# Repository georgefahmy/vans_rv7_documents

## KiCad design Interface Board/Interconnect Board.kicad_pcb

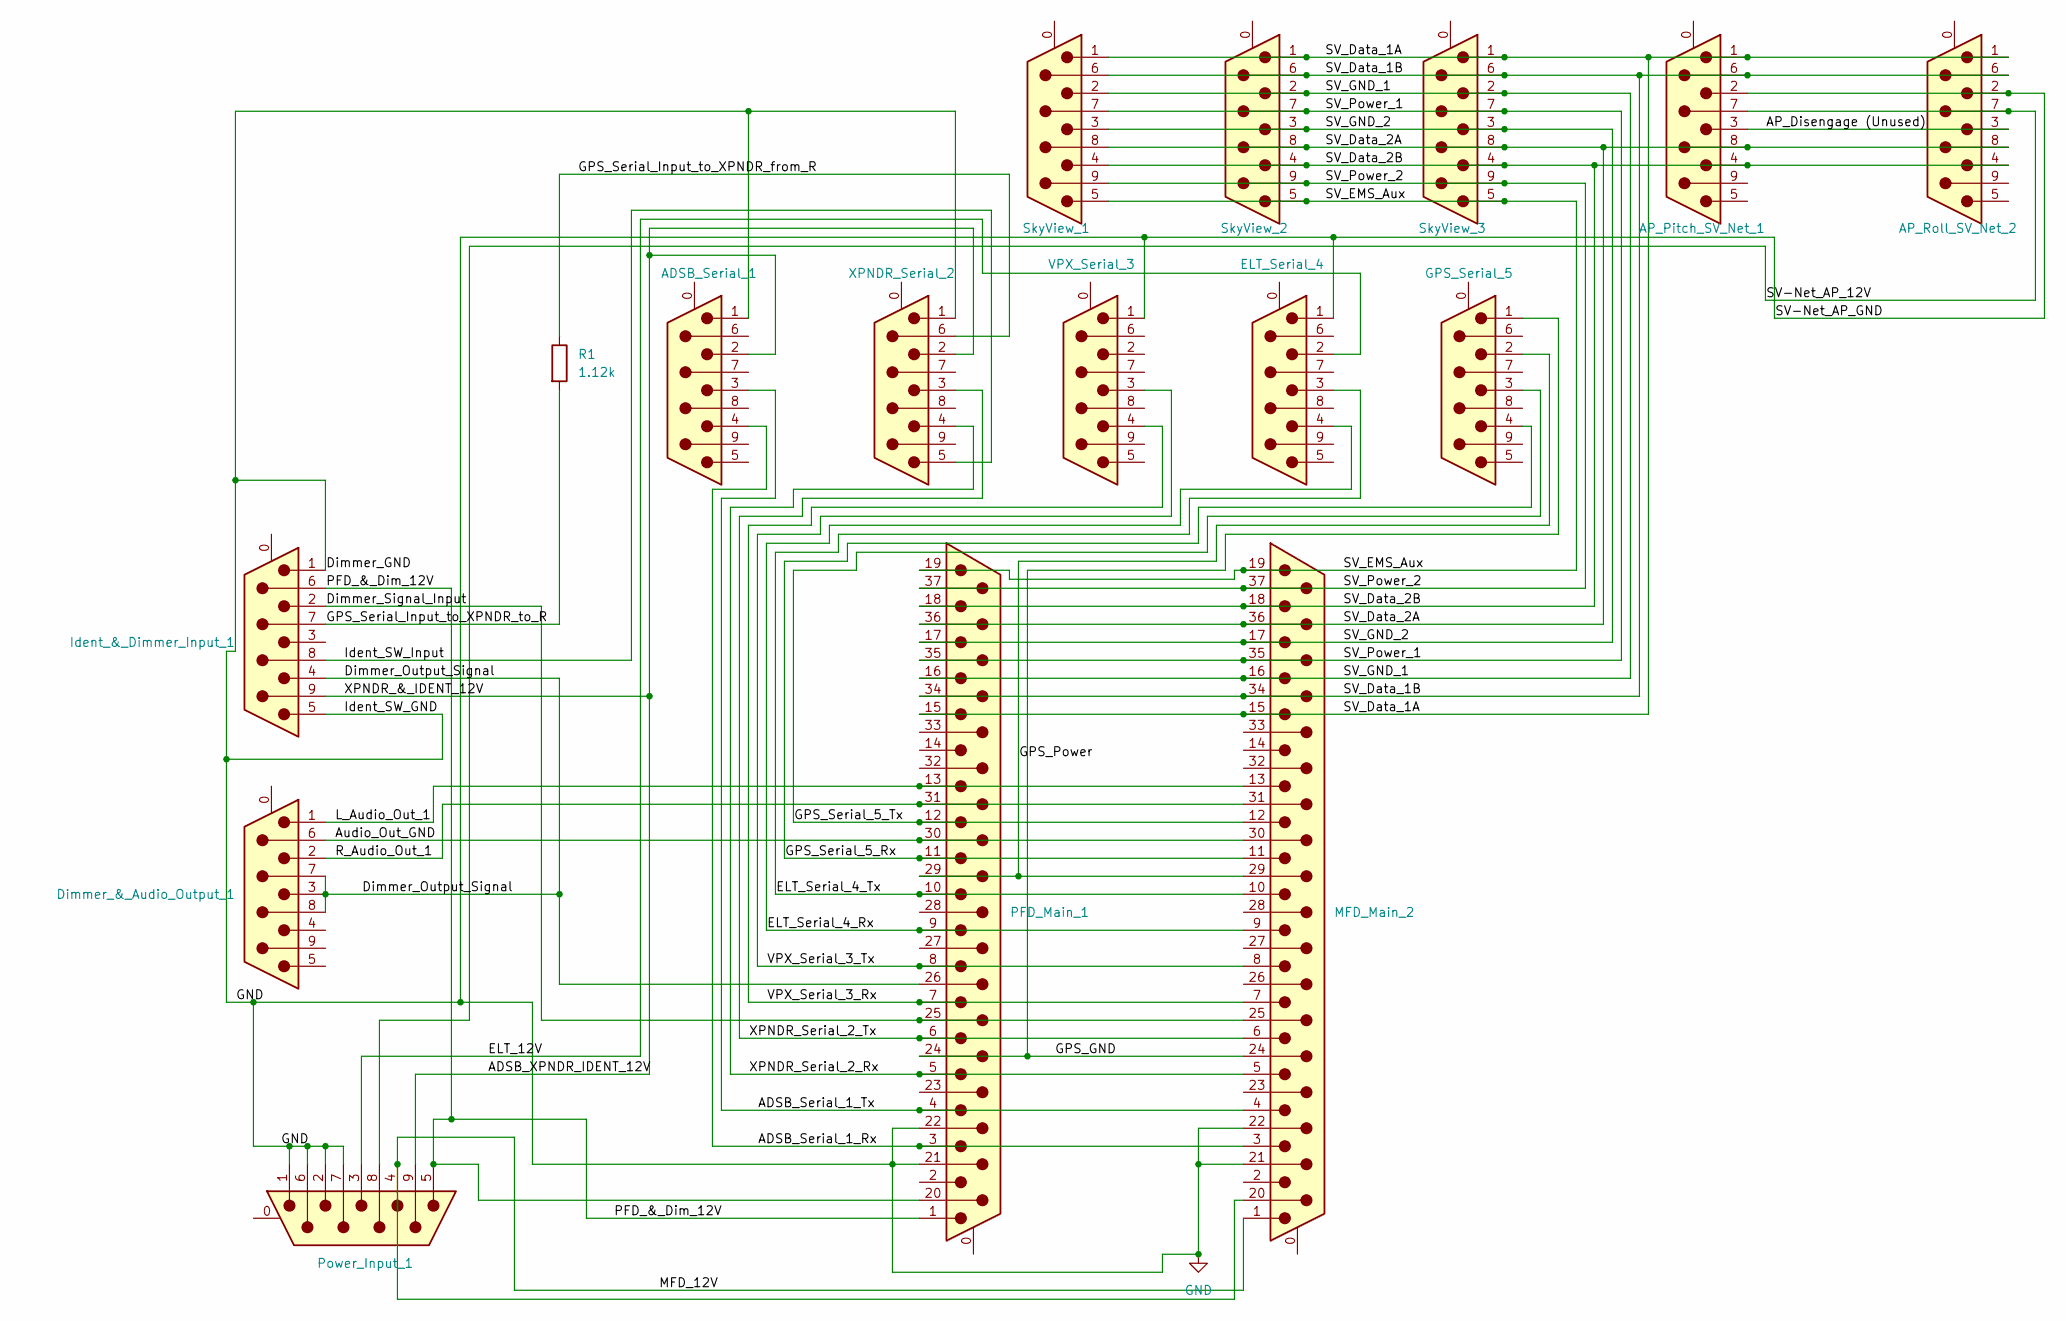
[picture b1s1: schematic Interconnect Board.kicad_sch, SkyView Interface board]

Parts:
ADSB_Serial_1: DE9_Plug_MountingHoles; DSUB-9_Male_Vertical_P2.77x2.84mm_MountingHoles
AP_Pitch_SV_Net_1: DE9_Plug_MountingHoles; DSUB-9_Male_Vertical_P2.77x2.84mm_MountingHoles
AP_Roll_SV_Net_2: DE9_Plug_MountingHoles; DSUB-9_Male_Vertical_P2.77x2.84mm_MountingHoles
Dimmer_&_Audio_Output_1: DE9_Plug_MountingHoles; DSUB-9_Male_Vertical_P2.77x2.84mm_MountingHoles
ELT_Serial_4: DE9_Plug_MountingHoles; DSUB-9_Male_Vertical_P2.77x2.84mm_MountingHoles
GPS_Serial_5: DE9_Plug_MountingHoles; DSUB-9_Male_Vertical_P2.77x2.84mm_MountingHoles
Ident_&_Dimmer_Input_1: DE9_Plug_MountingHoles; DSUB-9_Male_Vertical_P2.77x2.84mm_MountingHoles
MFD_Main_2: DC37_Plug_MountingHoles; DSUB-37_Male_Vertical_P2.77x2.84mm_MountingHoles
PFD_Main_1: DC37_Plug_MountingHoles; DSUB-37_Male_Vertical_P2.77x2.84mm_MountingHoles
Power_Input_1: DE9_Plug_MountingHoles; DSUB-9_Male_Vertical_P2.77x2.84mm_MountingHoles
R1: 1.12k; R_Axial_DIN0207_L6.3mm_D2.5mm_P10.16mm_Horizontal
SkyView_1, SkyView_2, SkyView_3: DE9_Plug_MountingHoles; DSUB-9_Male_Vertical_P2.77x2.84mm_MountingHoles
VPX_Serial_3: DE9_Plug_MountingHoles; DSUB-9_Male_Vertical_P2.77x2.84mm_MountingHoles
XPNDR_Serial_2: DE9_Plug_MountingHoles; DSUB-9_Male_Vertical_P2.77x2.84mm_MountingHoles

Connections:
/ADSB_Serial_1_Rx: ADSB_Serial_1.4, MFD_Main_2.3, PFD_Main_1.3
/ADSB_Serial_1_Tx: ADSB_Serial_1.3, MFD_Main_2.4, PFD_Main_1.4
/ADSB_XPNDR_IDENT_12V: ADSB_Serial_1.2, Ident_&_Dimmer_Input_1.9, Power_Input_1.9, XPNDR_Serial_2.2
/AP_Disengage (Unused): AP_Pitch_SV_Net_1.3, AP_Roll_SV_Net_2.3
/Audio_Out_GND: Dimmer_&_Audio_Output_1.6, MFD_Main_2.30, PFD_Main_1.30
/Dimmer_Output_Signal: Dimmer_&_Audio_Output_1.3, Dimmer_&_Audio_Output_1.7, Dimmer_&_Audio_Output_1.8, Ident_&_Dimmer_Input_1.4, PFD_Main_1.26
/Dimmer_Signal_Input: Ident_&_Dimmer_Input_1.2, MFD_Main_2.25, PFD_Main_1.25
/ELT_12V: ELT_Serial_4.2, Power_Input_1.3
/ELT_Serial_4_Rx: ELT_Serial_4.4, MFD_Main_2.9, PFD_Main_1.9
/ELT_Serial_4_Tx: ELT_Serial_4.3, MFD_Main_2.10, PFD_Main_1.10
/GPS_GND: GPS_Serial_5.1, MFD_Main_2.24, PFD_Main_1.24
/GPS_Power: GPS_Serial_5.2, MFD_Main_2.29, PFD_Main_1.29
/GPS_Serial_5_Rx: GPS_Serial_5.4, MFD_Main_2.11, PFD_Main_1.11
/GPS_Serial_5_Tx: GPS_Serial_5.3, MFD_Main_2.12, PFD_Main_1.12
/GPS_Serial_Input_to_XPNDR_from_R: R1.1, XPNDR_Serial_2.6
/GPS_Serial_Input_to_XPNDR_to_R: Ident_&_Dimmer_Input_1.7, R1.2
/Ident_SW_Input: Ident_&_Dimmer_Input_1.8, XPNDR_Serial_2.5
/L_Audio_Out_1: Dimmer_&_Audio_Output_1.1, MFD_Main_2.13, PFD_Main_1.13
/MFD_12V: MFD_Main_2.1, MFD_Main_2.20, Power_Input_1.4
/PFD_&_Dim_12V: Ident_&_Dimmer_Input_1.6, PFD_Main_1.1, PFD_Main_1.20, Power_Input_1.5
/R_Audio_Out_1: Dimmer_&_Audio_Output_1.2, MFD_Main_2.31, PFD_Main_1.31
/SV-Net_AP_12V: AP_Pitch_SV_Net_1.7, AP_Roll_SV_Net_2.7, Power_Input_1.8
/SV_Data_1A: AP_Pitch_SV_Net_1.1, AP_Roll_SV_Net_2.1, MFD_Main_2.15, PFD_Main_1.15, SkyView_1.1, SkyView_2.1, SkyView_3.1
/SV_Data_1B: AP_Pitch_SV_Net_1.6, AP_Roll_SV_Net_2.6, MFD_Main_2.34, PFD_Main_1.34, SkyView_1.6, SkyView_2.6, SkyView_3.6
/SV_Data_2A: AP_Pitch_SV_Net_1.8, AP_Roll_SV_Net_2.8, MFD_Main_2.36, PFD_Main_1.36, SkyView_1.8, SkyView_2.8, SkyView_3.8
/SV_Data_2B: AP_Pitch_SV_Net_1.4, AP_Roll_SV_Net_2.4, MFD_Main_2.18, PFD_Main_1.18, SkyView_1.4, SkyView_2.4, SkyView_3.4
/SV_EMS_Aux: MFD_Main_2.19, PFD_Main_1.19, SkyView_1.5, SkyView_2.5, SkyView_3.5
/SV_GND_1: MFD_Main_2.16, PFD_Main_1.16, SkyView_1.2, SkyView_2.2, SkyView_3.2
/SV_GND_2: MFD_Main_2.17, PFD_Main_1.17, SkyView_1.3, SkyView_2.3, SkyView_3.3
/SV_Power_1: MFD_Main_2.35, PFD_Main_1.35, SkyView_1.7, SkyView_2.7, SkyView_3.7
/SV_Power_2: MFD_Main_2.37, PFD_Main_1.37, SkyView_1.9, SkyView_2.9, SkyView_3.9
/VPX_Serial_3_Rx: MFD_Main_2.7, PFD_Main_1.7, VPX_Serial_3.4
/VPX_Serial_3_Tx: MFD_Main_2.8, PFD_Main_1.8, VPX_Serial_3.3
/XPNDR_Serial_2_Rx: MFD_Main_2.5, PFD_Main_1.5, XPNDR_Serial_2.4
/XPNDR_Serial_2_Tx: MFD_Main_2.6, PFD_Main_1.6, XPNDR_Serial_2.3
GND: ADSB_Serial_1.1, AP_Pitch_SV_Net_1.2, AP_Roll_SV_Net_2.2, ELT_Serial_4.1, Ident_&_Dimmer_Input_1.1, Ident_&_Dimmer_Input_1.5, MFD_Main_2.21, MFD_Main_2.22, PFD_Main_1.21, PFD_Main_1.22, Power_Input_1.1, Power_Input_1.2, Power_Input_1.6, Power_Input_1.7, VPX_Serial_3.1, XPNDR_Serial_2.1

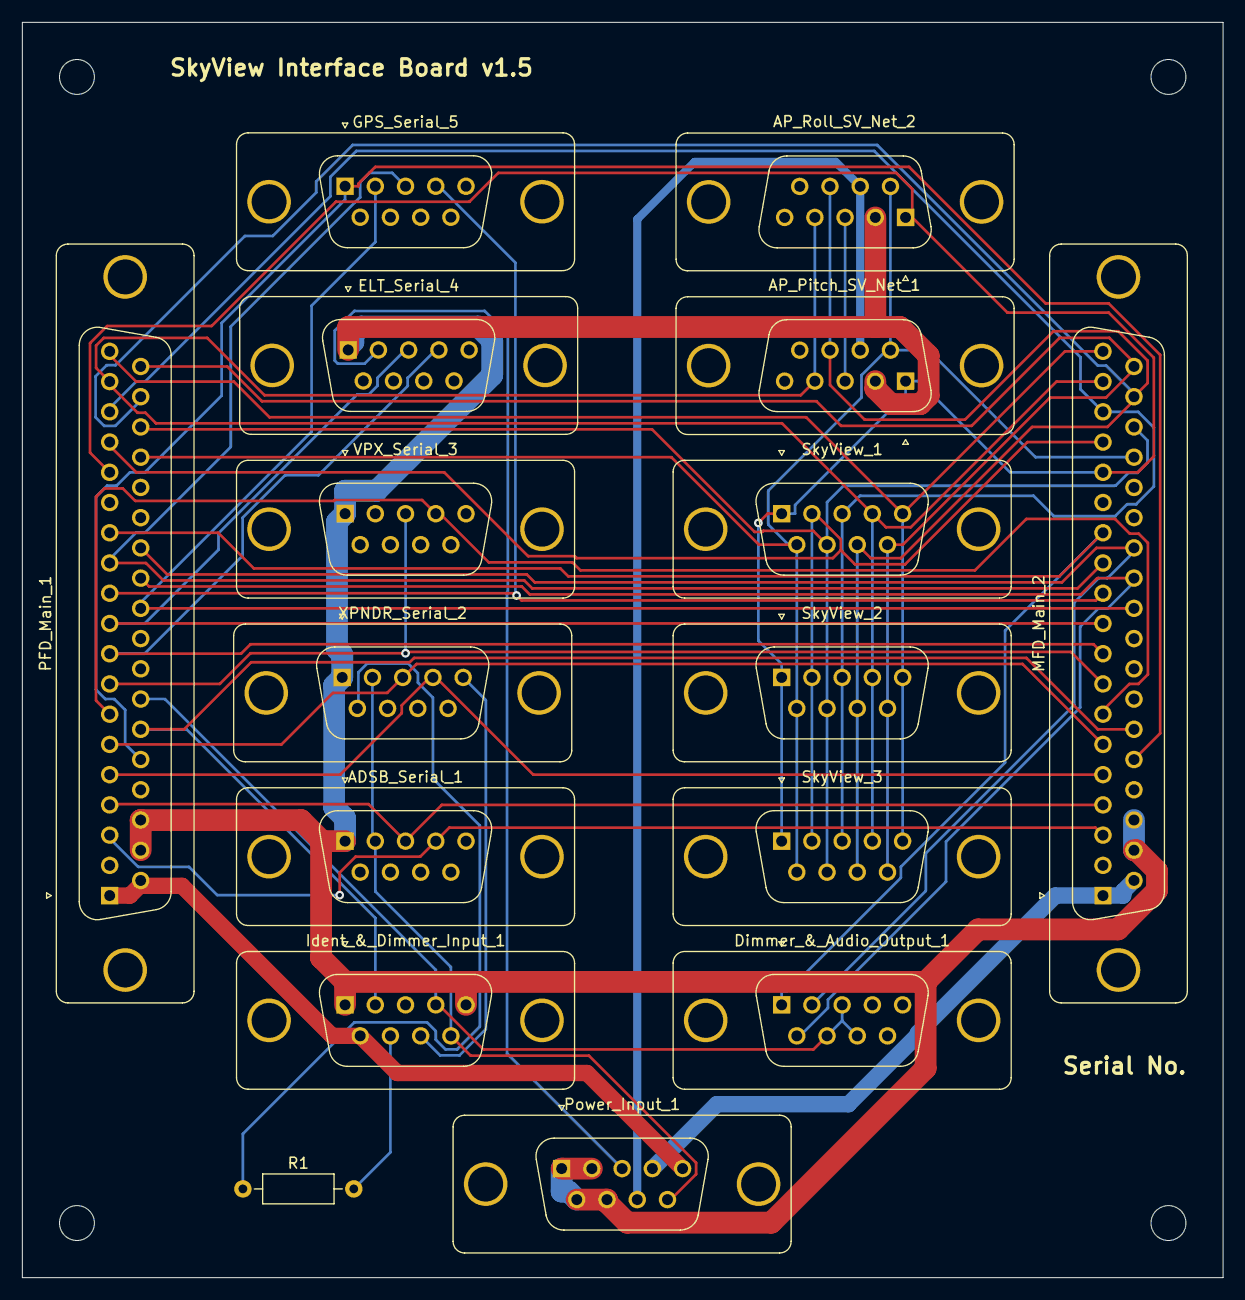
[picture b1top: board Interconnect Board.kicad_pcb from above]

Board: 2 copper layers, 110.0 x 115.0 mm, 20 parts (0 on the bottom side), 36 nets.

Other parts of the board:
MountingHole_1, MountingHole_2, MountingHole_3, MountingHole_4: MountingHole_3.2mm_M3

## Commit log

2025-11-04 update gitignore
2025-11-07 documentation updates and fixed checklist
2025-11-07 daily update
2025-11-19 gitignore
2025-11-30 gitignore clean up
2025-11-30 remove datalogs
2025-11-30 remove POHs
2025-12-08 documentation update
2026-01-06 new pdfs
